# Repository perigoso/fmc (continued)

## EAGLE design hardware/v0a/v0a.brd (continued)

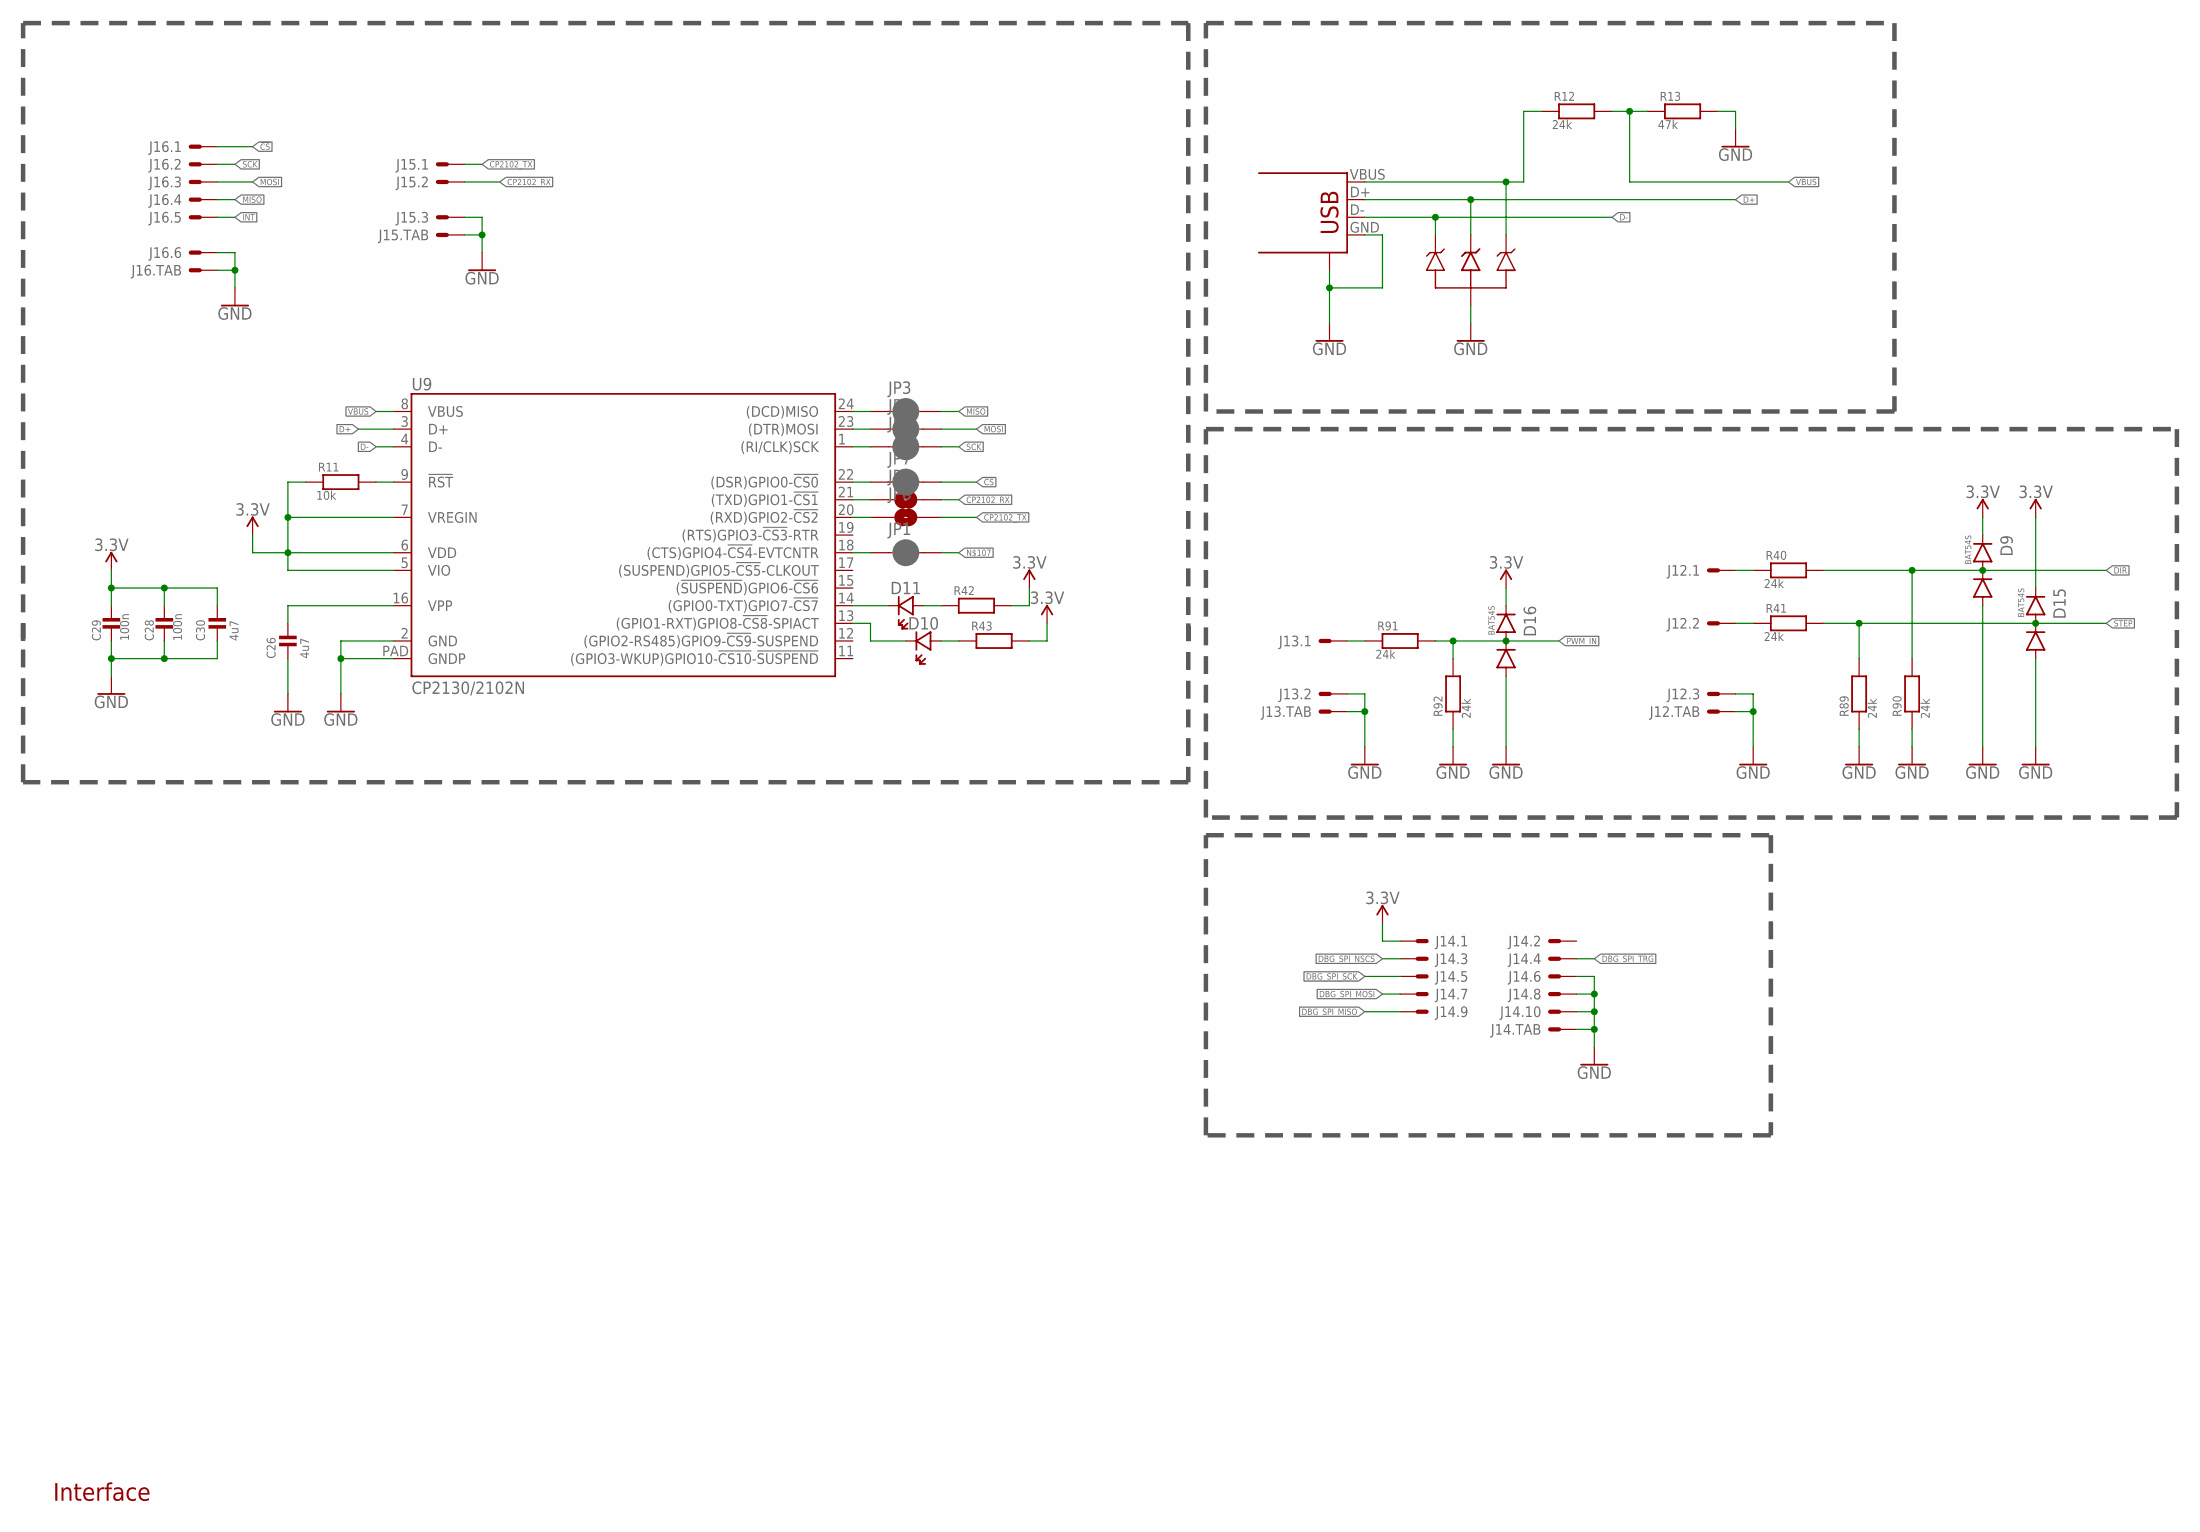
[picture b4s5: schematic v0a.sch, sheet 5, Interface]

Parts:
C26, C30: 4u7; 0603_WAVE
C28, C29: 100n; 0603_WAVE
D5: SP0503BAHT; SOT143
D9, D15, D16: BAT54S; SOT-23-3
D10, D11: LED0603; CHIPLED_0603
J12, J15: SH-3; SM03B-SSR-H-TB
J13: SH-2; SM02B-SSR-H-TB
J14: F20F-10DP-1V
J16: SH-6; SM06B-SSR-H-TB
JP1, JP3, JP4, JP5, JP7: JUMPER-SMT_2_NC_PASTE_SILK; SMT-JUMPER_2_NC_PASTE_SILK
JP2, JP6: JUMPER-SMT_2_NO_SILK; SMT-JUMPER_2_NO_SILK
R11: 10k; 0603_WAVE
R12, R40, R41, R89, R90, R91, R92: 24k; 0603_WAVE
R13: 47k; 0603_WAVE
R42, R43: RESISTOR0603; 0603_WAVE
U9: CP2130/2102N; QFN24
U$10: USB-SHIELD; USB-M-S1

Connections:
3.3V: C28.P$1, C29.P$1, C30.P$1, D9.P$2 (2), D15.P$2 (2), D16.P$2 (2), J14.1, R11.P$1, R42.P$2, R43.P$2, U9.5 (VIO), U9.6 (VDD), U9.7 (VREGIN); also elsewhere on the board
!CS: J16.1, JP7.2; also elsewhere on the board
CP2102_RX: J15.2, JP2.2; also elsewhere on the board
CP2102_TX: J15.1, JP6.2; also elsewhere on the board
D+: D5.3, U9.3 (D+), U$10.D+
D-: D5.2, U9.4 (D-), U$10.D-
DBG_SPI_MISO: J14.9; also elsewhere on the board
DBG_SPI_MOSI: J14.7; also elsewhere on the board
DBG_SPI_NSCS: J14.3; also elsewhere on the board
DBG_SPI_SCK: J14.5; also elsewhere on the board
DBG_SPI_TRG: J14.4; also elsewhere on the board
DIR: D9.P$3 (3), R40.P$2, R90.P$2; also elsewhere on the board
GND: C26.P$2, C28.P$2, C29.P$2, C30.P$2, D5.1, D9.P$1 (1), D15.P$1 (1), D16.P$1 (1), J12.3, J12.FIT@1, J12.FIT@2, J13.2, J13.FIT@1, J13.FIT@2, J14.6, J14.8, J14.10, J14.TAB1, J14.TAB2, J15.3, J15.FIT@1, J15.FIT@2, J16.6, J16.FIT@1, J16.FIT@2, R13.P$2, R89.P$1, R90.P$1, R92.P$1, U9.2 (GND), U9.PAD (GNDP), U$10.GND, U$10.GND@1 (CASE), U$10.GND@2 (CASE), U$10.GND@3 (CASE), U$10.GND@4 (CASE); also elsewhere on the board
INT: J16.5; also elsewhere on the board
MISO: J16.4, JP3.2; also elsewhere on the board
MOSI: J16.3, JP4.2; also elsewhere on the board
unnamed: D5.4, R12.P$1, U$10.VBUS
unnamed: J12.2, R41.P$1
unnamed: R11.P$2, U9.9 (!RST)
unnamed: C26.P$1, U9.16 (VPP)
unnamed: J12.1, R40.P$1
unnamed: J13.1, R91.P$1
unnamed: D11.C (CA), U9.14 ((GPIO0-TXT)GPIO7-!CS7)
unnamed: D10.C (CA), U9.13 ((GPIO1-RXT)GPIO8-!CS8!-SPIACT)
unnamed: D11.A (AN), R42.P$1
unnamed: D10.A (AN), R43.P$1
unnamed: JP6.1, U9.20 ((RXD)GPIO2-!CS2)
unnamed: JP2.1, U9.21 ((TXD)GPIO1-!CS1)
unnamed: JP1.1, U9.18 ((CTS)GPIO4-!CS4!-EVTCNTR)
unnamed: JP7.1, U9.22 ((DSR)GPIO0-!CS0)
unnamed: JP5.1, U9.1 ((RI/CLK)SCK)
unnamed: JP4.1, U9.23 ((DTR)MOSI)
unnamed: JP3.1, U9.24 ((DCD)MISO)
PWM_IN: D16.P$3 (3), R91.P$2, R92.P$2; also elsewhere on the board
SCK: J16.2, JP5.2; also elsewhere on the board
STEP: D15.P$3 (3), R41.P$2, R89.P$2; also elsewhere on the board
VBUS: R12.P$2, R13.P$1, U9.8 (VBUS)

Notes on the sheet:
Interface

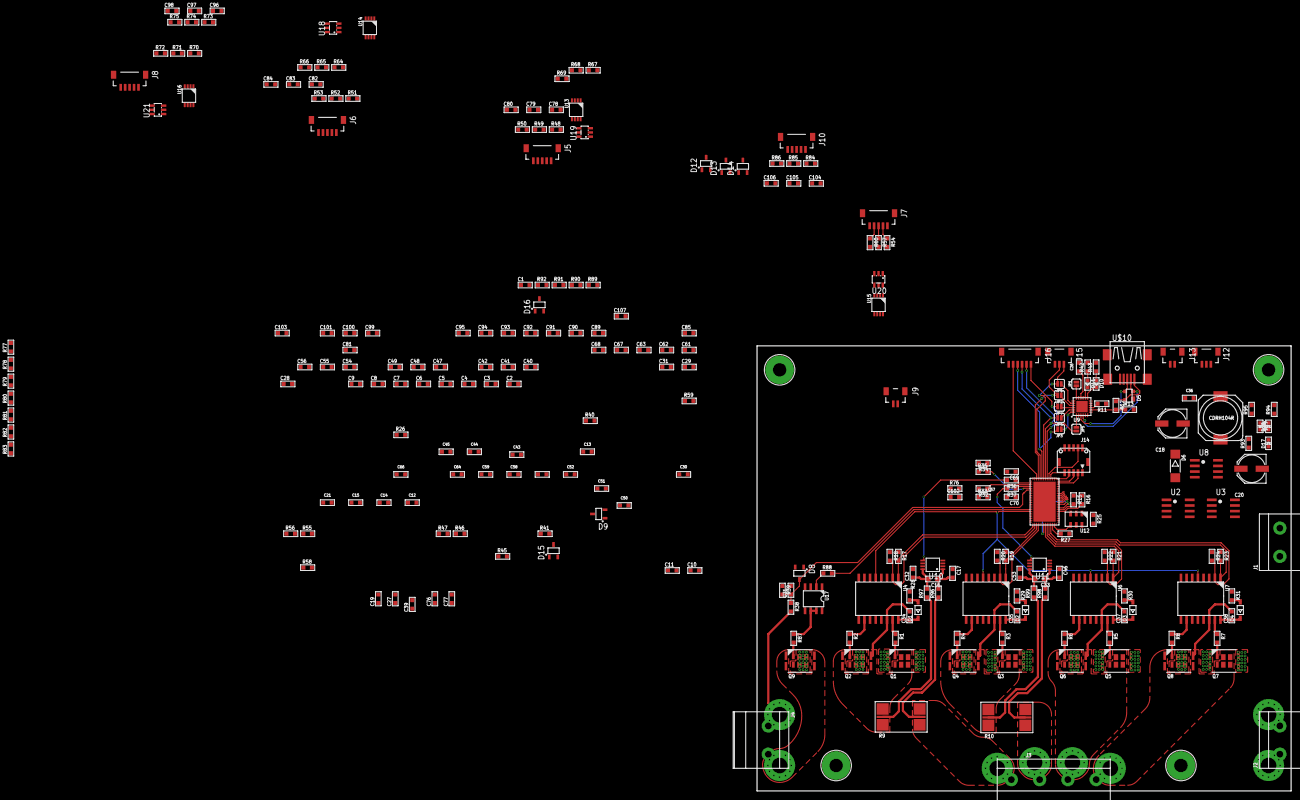
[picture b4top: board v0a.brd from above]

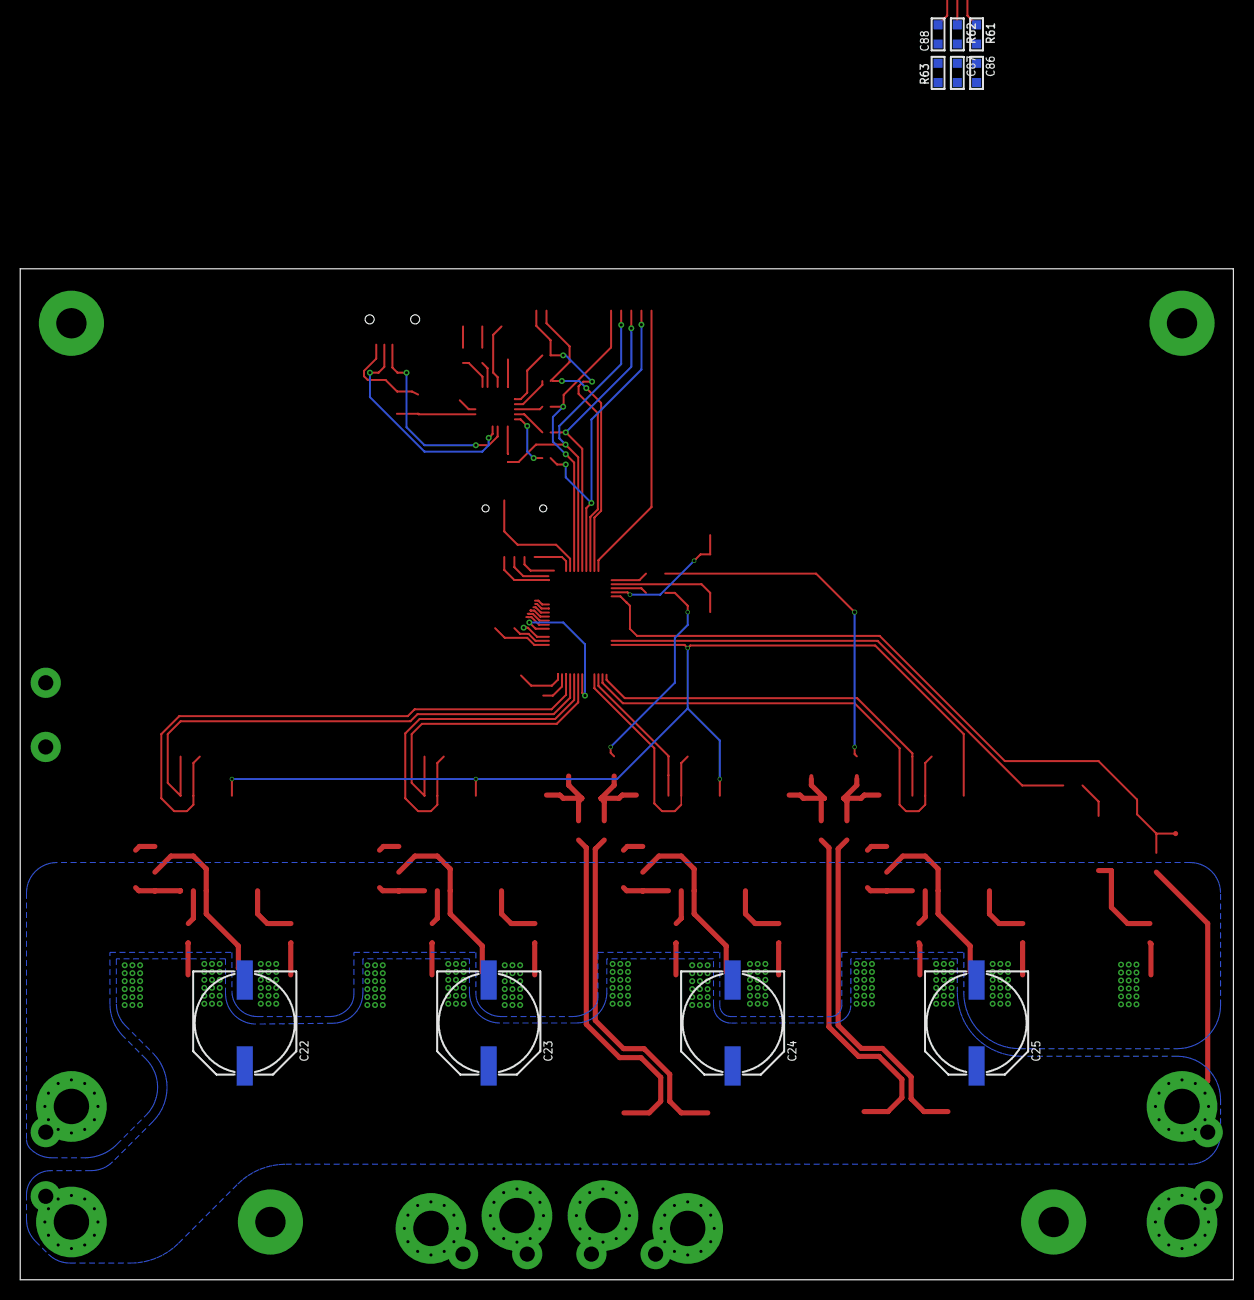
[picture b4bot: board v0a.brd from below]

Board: 2 copper layers, 120.0 x 100.0 mm, 282 parts (10 on the bottom side), 161 nets.

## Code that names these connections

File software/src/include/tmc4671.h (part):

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#define TMC4671_INTERIM_ADDR_SHIFT                           0 // min.: 0, max.: 215, default: 0
#define TMC4671_WATCHDOG_CFG_MASK                            0x03 // WATCHDOG_CFG //
#define TMC4671_WATCHDOG_CFG_SHIFT                           0 // min.: 0, max.: 3, default: 0
#define TMC4671_ADC_VM_LIMIT_LOW_MASK                        0xFFFF // ADC_VM_LIMITS // Low limit for brake chopper output BRAKE_OUT.
#define TMC4671_ADC_VM_LIMIT_LOW_SHIFT                       0 // min.: 0, max.: 65535, default: 0
#define TMC4671_ADC_VM_LIMIT_HIGH_MASK                       0xFFFF0000 // ADC_VM_LIMITS // High limit for brake chopper output BRAKE_OUT.
#define TMC4671_ADC_VM_LIMIT_HIGH_SHIFT                      16 // min.: 0, max.: 65535, default: 0
#define TMC4671_A_OF_ABN_RAW_MASK                            0x01 // TMC4671_INPUTS_RAW // A of ABN_RAW
#define TMC4671_A_OF_ABN_RAW_SHIFT                           0 // min.: 0, max.: 1, default: 0
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#define TMC4671_B_OF_ABN_2_RAW_SHIFT                         5 // min.: 0, max.: 1, default: 0
#define TMC4671_N_OF_ABN_2_RAW_MASK                          0x40 // TMC4671_INPUTS_RAW // N of ABN_2_RAW
#define TMC4671_N_OF_ABN_2_RAW_SHIFT                         6 // min.: 0, max.: 1, default: 0
#define TMC4671_HALL_UX_OF_HALL_RAW_MASK                     0x0100 // TMC4671_INPUTS_RAW // HALL_UX of HALL_RAW
#define TMC4671_HALL_UX_OF_HALL_RAW_SHIFT                    8 // min.: 0, max.: 1, default: 0
#define TMC4671_HALL_V_OF_HALL_RAW_MASK                      0x0200 // TMC4671_INPUTS_RAW // HALL_V of HALL_RAW
#define TMC4671_HALL_V_OF_HALL_RAW_SHIFT                     9 // min.: 0, max.: 1, default: 0
#define TMC4671_HALL_WY_OF_HALL_RAW_MASK                     0x0400 // TMC4671_INPUTS_RAW // HALL_WY of HALL_RAW
#define TMC4671_HALL_WY_OF_HALL_RAW_SHIFT                    10 // min.: 0, max.: 1, default: 0
#define TMC4671_REF_SW_R_RAW_MASK                            0x1000 // TMC4671_INPUTS_RAW // REF_SW_R_RAW
#define TMC4671_REF_SW_R_RAW_SHIFT                           12 // min.: 0, max.: 1, default: 0
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#define TMC4671_PWM_IDLE_L_RAW_SHIFT                         28 // min.: 0, max.: 1, default: 0
#define TMC4671_PWM_IDLE_H_RAW_MASK                          0x20000000 // TMC4671_INPUTS_RAW // PWM_IDLE_H_RAW
#define TMC4671_PWM_IDLE_H_RAW_SHIFT                         29 // min.: 0, max.: 1, default: 0
#define TMC4671_OUTPUTS_RAW_0_MASK                           0x01 // TMC4671_OUTPUTS_RAW // PWM_UX1_L
#define TMC4671_OUTPUTS_RAW_0_SHIFT                          0 // min.: 0, max.: 1, default: 0
#define TMC4671_OUTPUTS_RAW_1_MASK                           0x02 // TMC4671_OUTPUTS_RAW // PWM_UX1_H
#define TMC4671_OUTPUTS_RAW_1_SHIFT                          1 // min.: 0, max.: 1, default: 0
#define TMC4671_OUTPUTS_RAW_2_MASK                           0x04 // TMC4671_OUTPUTS_RAW // PWM_VX2_L
#define TMC4671_OUTPUTS_RAW_2_SHIFT                          2 // min.: 0, max.: 1, default: 0
#define TMC4671_OUTPUTS_RAW_3_MASK                           0x08 // TMC4671_OUTPUTS_RAW // PWM_VX2_H
#define TMC4671_OUTPUTS_RAW_3_SHIFT                          3 // min.: 0, max.: 1, default: 0
#define TMC4671_OUTPUTS_RAW_4_MASK                           0x10 // TMC4671_OUTPUTS_RAW // PWM_WY1_L
#define TMC4671_OUTPUTS_RAW_4_SHIFT                          4 // min.: 0, max.: 1, default: 0
#define TMC4671_OUTPUTS_RAW_5_MASK                           0x20 // TMC4671_OUTPUTS_RAW // PWM_WY1_H
#define TMC4671__OUTPUTS_RAW_5_SHIFT                          5 // min.: 0, max.: 1, default: 0
#define TMC4671_OUTPUTS_RAW_6_MASK                           0x40 // TMC4671_OUTPUTS_RAW // PWM_Y2_L
#define TMC4671_OUTPUTS_RAW_6_SHIFT                          6 // min.: 0, max.: 1, default: 0
#define TMC4671_OUTPUTS_RAW_7_MASK                           0x80 // TMC4671_OUTPUTS_RAW // PWM_Y2_H
#define TMC4671_OUTPUTS_RAW_7_SHIFT                          7 // min.: 0, max.: 1, default: 0
#define TMC4671_STEP_WIDTH_MASK                              0xFFFFFFFF // STEP_WIDTH // STEP WIDTH = 0 => STP pulses ignored, resulting direction = DIR XOR sign(STEP_WIDTH), effects PID_POSITION_TARGET
#define TMC4671_STEP_WIDTH_SHIFT                             0 // min.: -2147483648, max.: 2147483647, default: 0
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#define TMC4671_STATUS_FLAGS_26_SHIFT                        26 // min.: 0, max.: 1, default: 0
#define TMC4671_STATUS_FLAGS_27_MASK                         0x08000000 // STATUS_FLAGS // aenc_clipped
#define TMC4671_STATUS_FLAGS_27_SHIFT                        27 // min.: 0, max.: 1, default: 0
#define TMC4671_STATUS_FLAGS_28_MASK                         0x10000000 // STATUS_FLAGS // enc_n
#define TMC4671_STATUS_FLAGS_28_SHIFT                        28 // min.: 0, max.: 1, default: 0
#define TMC4671_STATUS_FLAGS_29_MASK                         0x20000000 // STATUS_FLAGS // enc_2_n
#define TMC4671_STATUS_FLAGS_29_SHIFT                        29 // min.: 0, max.: 1, default: 0
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
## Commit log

2019-03-24 Started Documentation and sch
2019-03-25 rough schematic and component requirement defenition
2019-03-25 temp
2019-03-26 nothing
2019-03-27 changed current sense resistors to 700u
2019-03-27 sch work
2019-03-29 pcb work
2019-04-01 pcb 80% finished
2019-04-02 added pdf
2019-04-03 finished pcb, added pdf and png exports of pcb
2019-04-04 component request preparation
2019-04-04 component request
2019-04-05 bom component request
2019-04-05 request changes
2019-04-10 added Documentation
2019-04-11 documentation
2019-04-14 update readme, add license
2019-05-15 added tagconnect to bom
2019-05-15 fixed bom inconsintency
2019-05-23 doc edit
2019-05-28 started software development
2019-05-28 remove vscode bloat
2019-05-28 tmc4671 api work
2019-05-29 minor canges
2019-05-29 api finished, initial testing
2019-06-05 workin BOI
2019-06-06 please work for the love of god
2019-06-11 feedback testing
2019-06-14 ft4222h breakout
2019-12-09 fixed current measuring, still can't make it work
